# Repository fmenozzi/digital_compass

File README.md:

A digital compass that uses an LED ring to display the compass rose.

Upon startup, the compass enters magnetometer calibration mode, shown by the led chase sequence:

https://github.com/fmenozzi/digital_compass/assets/4451432/49a2e2fe-652e-430a-9320-a2c4e0b69866

During calibration, the compass should be moved around in all directions. Calibration ends after calibrated values do not change for five seconds.

Once the chase sequence ends, the compass rose will be displayed and the compass is now active, with the red LED pointing *very roughly* north:

https://github.com/fmenozzi/digital_compass/assets/4451432/9e37ce8d-d3a7-4e10-ac38-1c5cc8147863

Accuracy will suffer for a couple of reasons, such as being limited to only 24 possible directions and the magnetometer calibration being suboptimal. Regardless, this was a fun little proof-of-concept project for me, and my first non-trivial hardware project.

The microcontroller is a Seeeduino Xiao, and the magnetometer board uses the QMC5883L chip. The LED ring is an Adafruit Neopixel Ring 24, and a basic level shifter board does the conversions between the Xiao's needed 3.3V and 5V.

The software was programmed using Arduino. The circuit board was designed in KiCAD and manufactured by JLCPCB. The 3D-printed enclosure was designed in FreeCAD.

All software, schematics, and design files are licensed under the [MIT license](https://mit-license.org/).

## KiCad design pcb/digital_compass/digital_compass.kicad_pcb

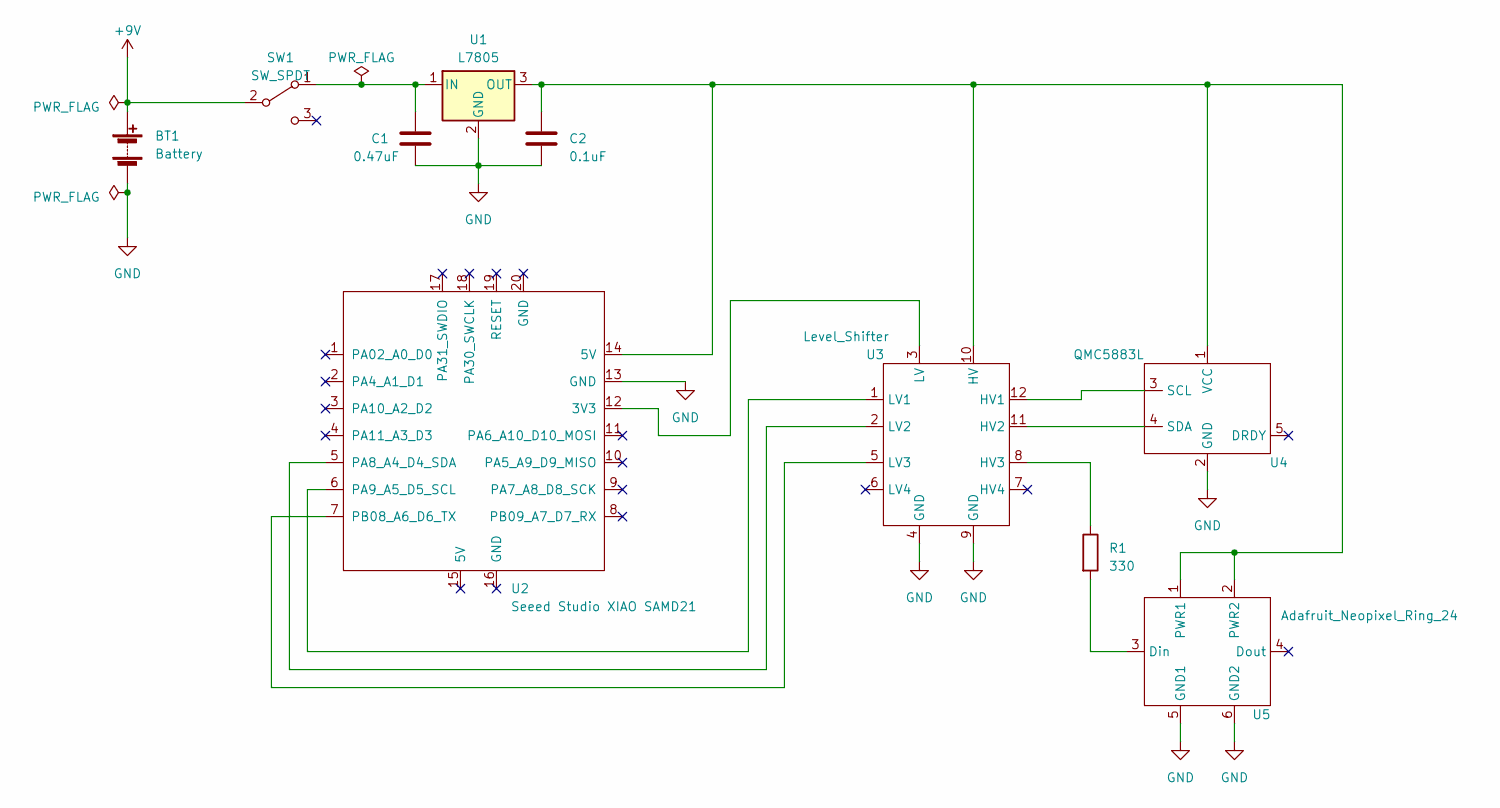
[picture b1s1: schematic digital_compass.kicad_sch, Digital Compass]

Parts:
BT1: Battery; BatteryHolder_Eagle_12BH611-GR
C1: 0.47uF; C_1206_3216Metric_Pad1.33x1.80mm_HandSolder
C2: 0.1uF; C_1206_3216Metric_Pad1.33x1.80mm_HandSolder
R1: 330; R_1206_3216Metric_Pad1.30x1.75mm_HandSolder
SW1: SW_SPDT; JS102011SCQN_SPDT_Switch
U1: L7805; TO-252-3_TabPin2
U2: Seeed Studio XIAO SAMD21; XIAO-SAMD21-RP2040-14P-2.54-21X17.8MM (Seeeduino XIAO)
U3: Level_Shifter
U4: QMC5883L
U5: Adafruit_Neopixel_Ring_24; Adafruit Neopixel Ring 24

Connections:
+9V: BT1.1 (+), SW1.2 (B)
GND: BT1.2 (-), C1.2, C2.2, U1.2 (GND), U2.13 (GND), U3.4 (GND), U3.9 (GND), U4.2 (GND), U5.5 (GND1), U5.6 (GND2)
unnamed: C1.1, SW1.1 (A), U1.1 (IN)
unnamed: C2.1, U1.3 (OUT), U2.14 (5V), U3.10 (HV), U4.1 (VCC), U5.1 (PWR1), U5.2 (PWR2)
unnamed: U2.12 (3V3), U3.3 (LV)
unnamed: U2.5 (PA8_A4_D4_SDA), U3.2 (LV2)
unnamed: U2.6 (PA9_A5_D5_SCL), U3.1 (LV1)
unnamed: U2.7 (PB08_A6_D6_TX), U3.5 (LV3)
unnamed: U3.12 (HV1), U4.3 (SCL)
unnamed: U3.11 (HV2), U4.4 (SDA)
unnamed: R1.1, U3.8 (HV3)
unnamed: R1.2, U5.3 (Din)

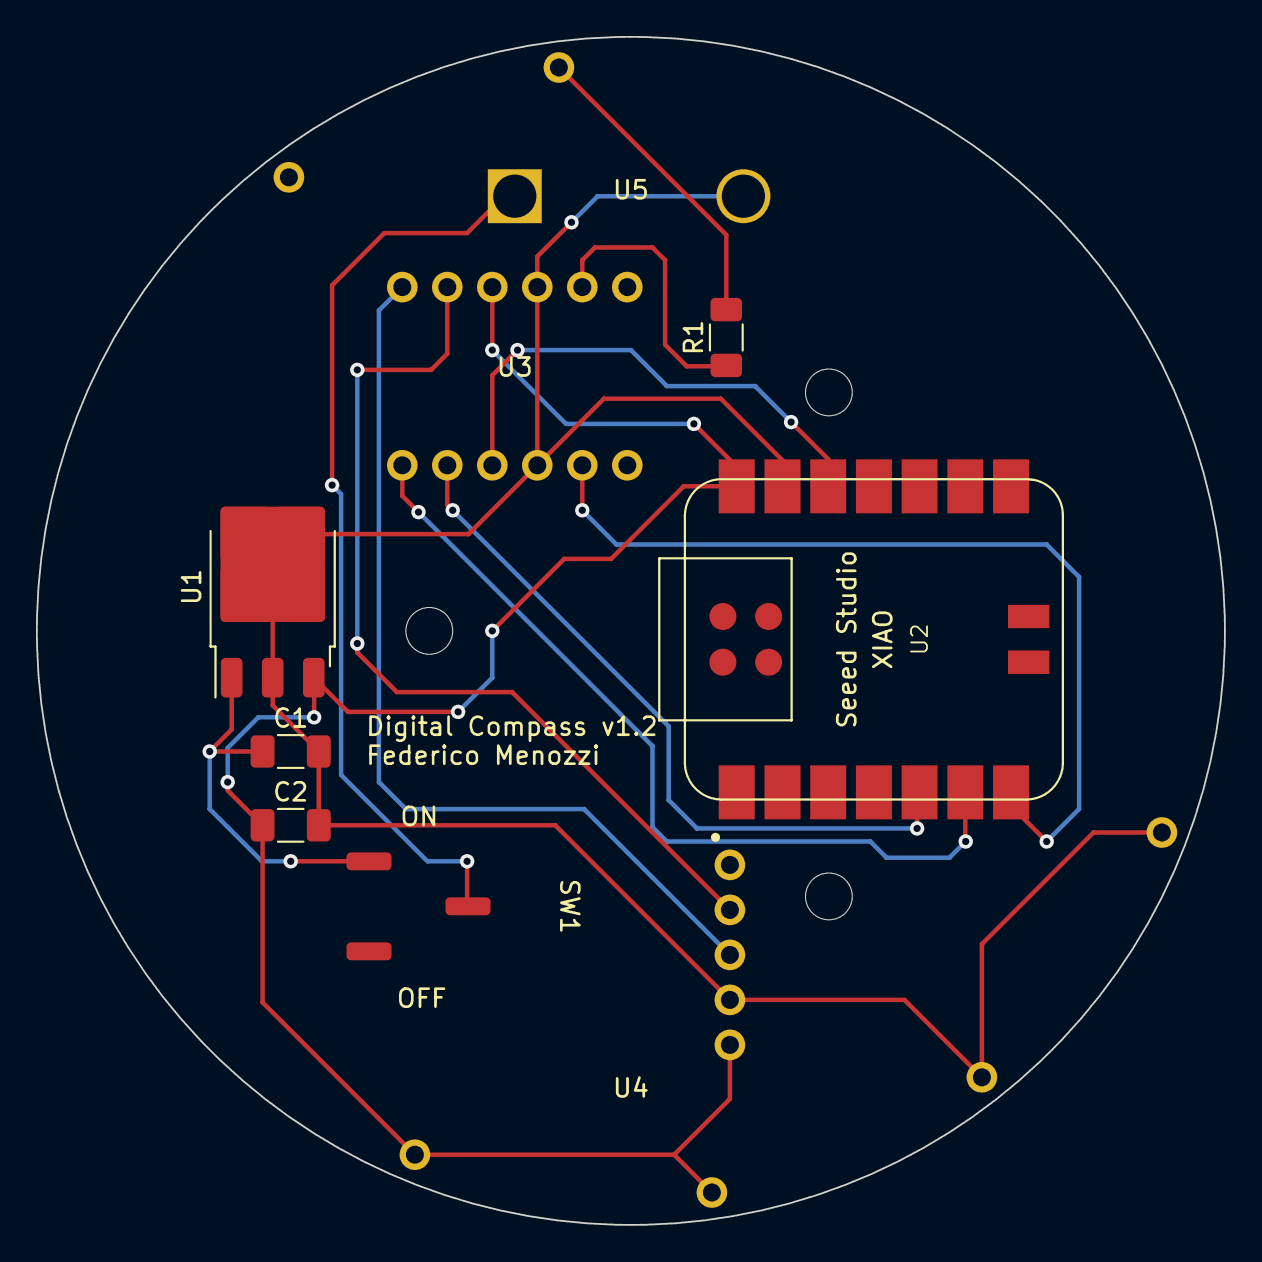
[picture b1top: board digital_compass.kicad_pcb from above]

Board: 2 copper layers, 66.0 x 66.0 mm, 10 parts (1 on the bottom side), 12 nets.

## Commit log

2022-11-28 Initial commit.
2022-12-10 Add preliminary code implementation.
    This code provides the bare-minimum functionality of a digital compass;
    that is, it measures the heading from the qmc5883l magnetometer and
    lights the appropriate leds on a 24-piece neopixel ring (i.e. in the
    cardinal directions).
    Future additions might include a debug mode for displaying magnetometer
    readings via serial, adding a calibration mode instead of hardcoding a
2022-12-10 Create empty kicad project.
2022-12-10 Add symbol for neopixel ring.
2022-12-11 Add initial footprint for neopixel ring 24.
    Not sure yet whether the hollow ring aspect was captured properly here.
2022-12-11 Add symbol for QMC5883L magnetometer.
2022-12-11 Add footprint for QMC588L.
2023-04-22 Finish basic digital compass schematic.
    * Based on updated xiao-based design
    * Also opened in KiCad 7
2023-04-23 Add/update footprints and run fp assignment.
    The footprints for the level shifter and magnetometer boards were
    created manually, but the xiao symbol/footprint were taken from
    https://github.com/Seeed-Studio/OPL_Kicad_Library.
    Note that the xiao symbol was lightly tweaked to pass ERC, as the pins
    were not properly labeled as power inputs/outputs, bidirectional, etc.
2023-04-23 Add CLEAN to .gitignore.
2023-04-23 Add SPDT slide power switch.
    For now we just choose an ok-looking smd footprint but we may need to
    make a custom one depending on what we actually find with suppliers.
2023-04-23 Use custom footprint for SPDT switch.
    Based on https://www.ckswitches.com/media/1422/js.pdf. Also move the
    switch to the regulated side of the L7805, as this switch can only
    handle up to 6V.
2023-04-23 Create initial layout (no traces).
    The magnetometer and level shifter boards may be changed to use
    throughhole footprints instead of smd, but the size/layout shouldn't
    need to change in that case.
2023-04-23 Update mag/shifter footprints to use THT pads.
2023-04-23 Add initial routing for pcb.
    This currently passes the existing design rule checks, though I may need
    to go back and tweak some placements once I add the JLCPCB-specific
    design rules as well.
2023-04-24 Update schematic date and add helper silkscreen.
    Silkscreen includes ON/OFF for the power switch and project
    name/version/author lines.
2023-04-24 Set up design rules/constraints for jlcpcb.
    Taken from https://jlcpcb.com/capabilities/pcb-capabilities.
    Also correct two existing DRC violations.
2023-04-24 Generate gerbers/drill files for jlcpcb.
2023-05-06 Calibrate automatically on startup.
2023-05-06 Fix magnetometer and update schematic/pcb/gerbers.
    Turns out the original v1 magnetometer footprint had the pins in reverse
    order, so update the footprint/schematic/pcb/gerbers for round two at
    jlcpcb.
2023-05-12 Fix power switch and update schematic/pcb/gerbers.
    Turns out the L7805 consumes power when connected to an input power
    source even if the output is disconnected. We therefore move the power
    switch to the input side of the regulator to prevent power consumption
    when the compass is turned off.
2023-05-12 First pass at an enclosure.
    For now this is a single simple bottom piece, a cylinder with a pocket
    to fit the battery holder. We intentionally did not incorporate any
    additive printer tolerance into measurements in order to see whether
    it's possible to get a snug fit without any additional parts/fasteners.
2024-01-15 Adjust enclosure tolerance for better fit.
2024-02-21 Add LICENSE.

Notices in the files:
pcb/digital_compass/digital_compass.kicad_sch:
License: MIT License (https://opensource.org/licenses/MIT)
